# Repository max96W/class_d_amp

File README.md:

# Class D amplifier
A discrete class D amplifier able to deliver 300 W into 4 Ohms

For further information please read docu.pdf/odt. Note that the design is not fully tested yet so do not expect it to work out of the box if you like to build it.

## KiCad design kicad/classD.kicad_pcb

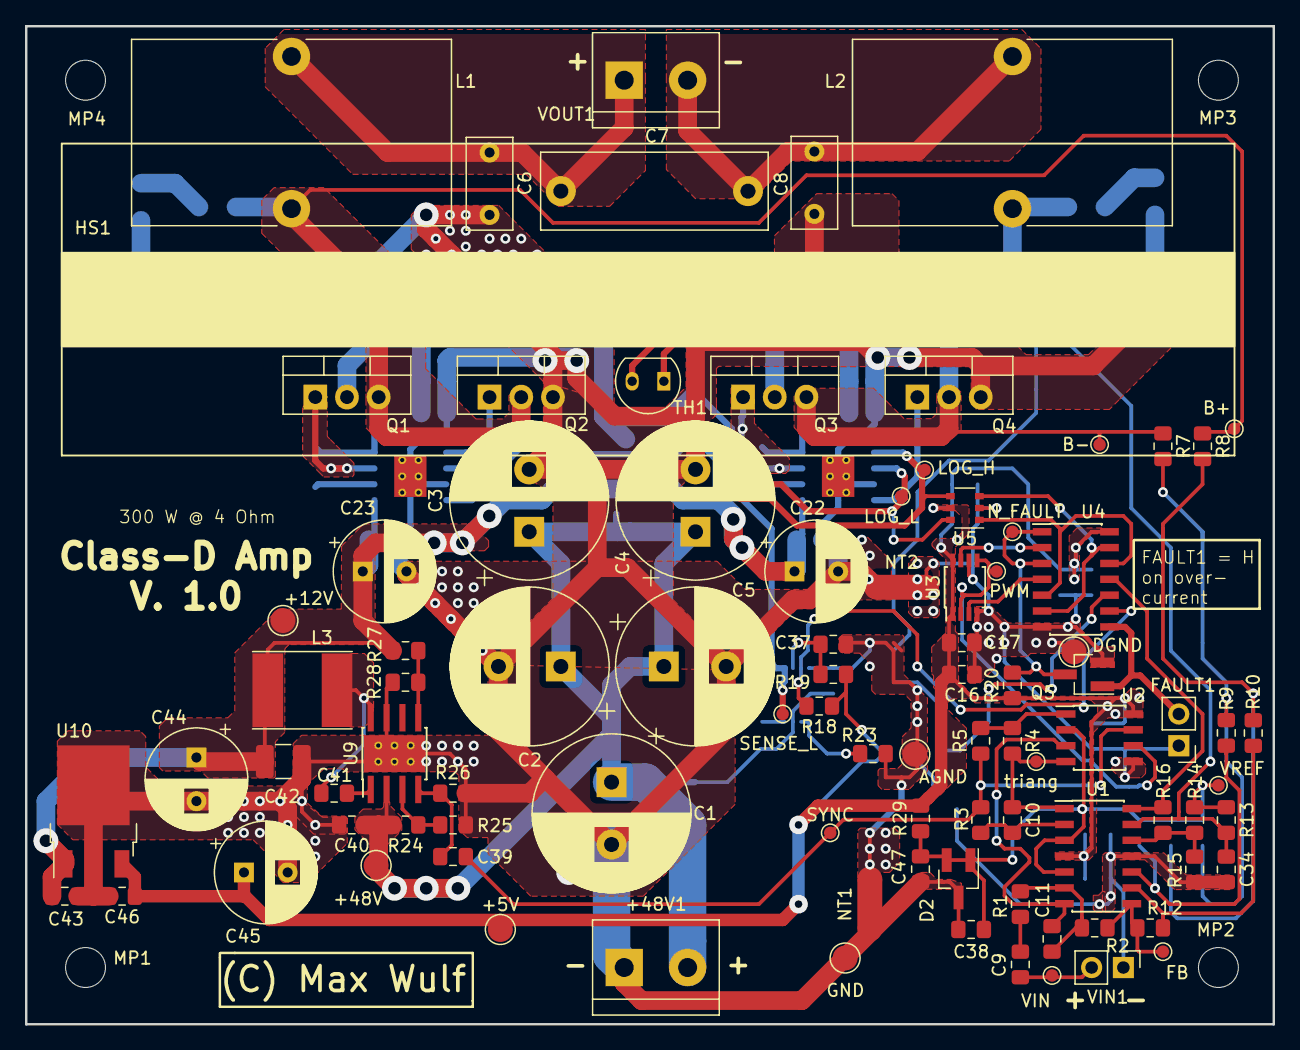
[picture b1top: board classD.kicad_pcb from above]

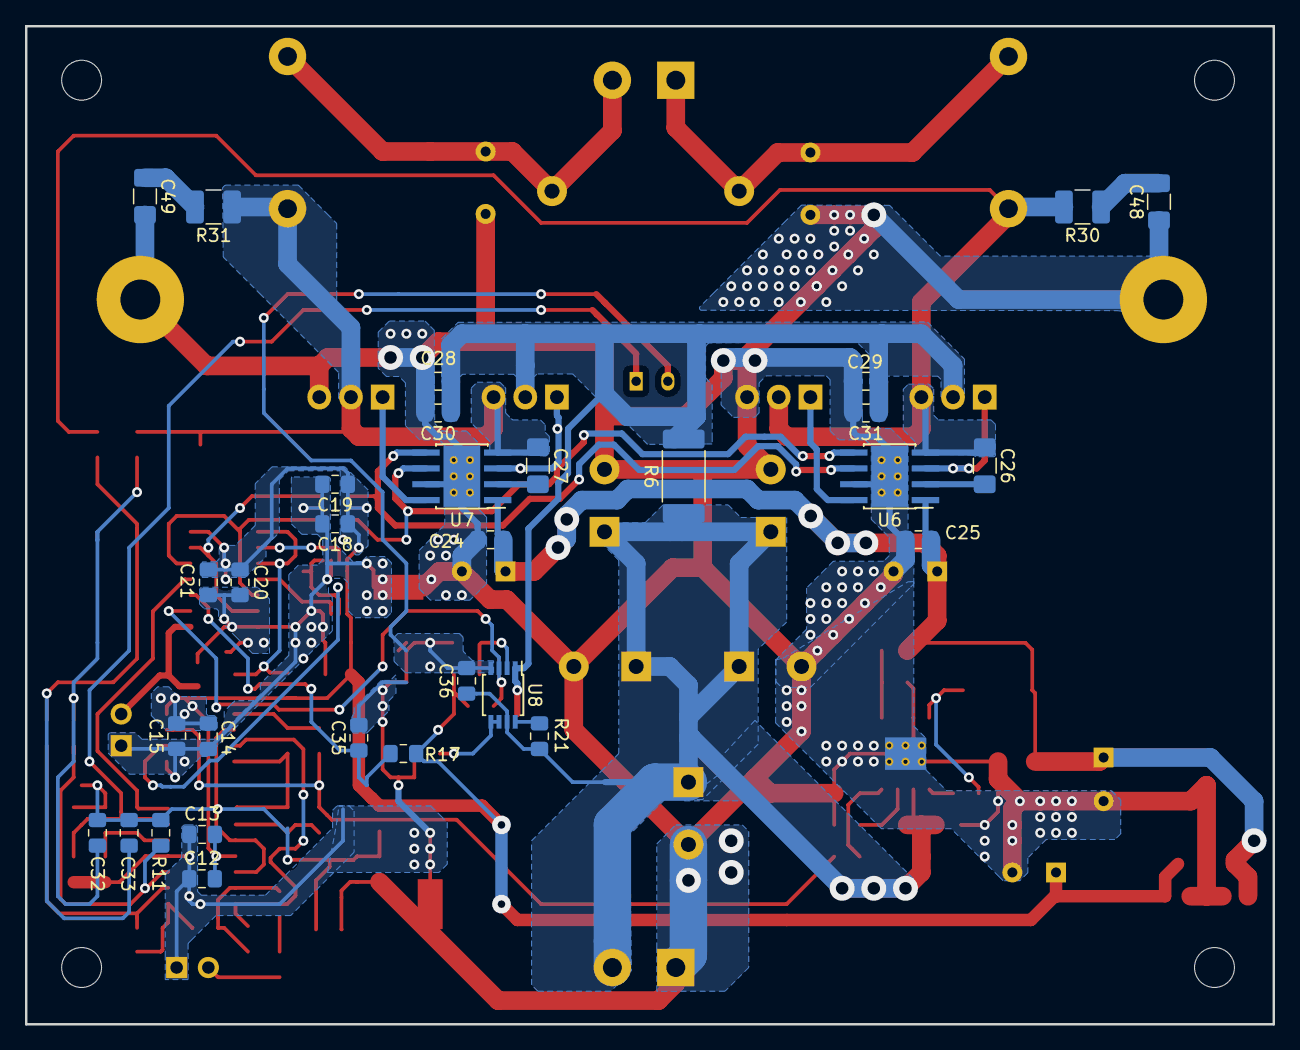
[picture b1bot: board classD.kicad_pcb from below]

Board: 2 copper layers, 100.0 x 80.0 mm, 128 parts (31 on the bottom side), 55 nets.

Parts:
+5V, +12V, +48V: TestPoint_Pad_D2.0mm
+48V1: 48V; TerminalBlock_bornier-2_P5.08mm
AGND: TestPoint_Pad_D2.0mm
B+: TestPoint_Pad_D1.0mm
B-: TestPoint_Pad_D1.0mm
C1, C2, C3, C4, C5: 470u/63V; CP_Radial_D12.5mm_P5.00mm
C6, C8: 270n/63 VDC; C_Rect_L7.2mm_W3.5mm_P5.00mm_FKS2_FKP2_MKS2_MKP2
C7: 1u/63 VAC; C_Rect_L18.0mm_W6.0mm_P15.00mm_FKS3_FKP3
C9: 2.2u; C_0805_2012Metric_Pad1.15x1.40mm_HandSolder
C10, C11: 33p; C_0805_2012Metric_Pad1.15x1.40mm_HandSolder
C12, C14, C16, C18, C20, C24, C25, C36, C37, C40, C41, C43, C46, C47: 100n; C_0805_2012Metric_Pad1.15x1.40mm_HandSolder
C13, C15, C17, C19, C21, C38: 10u; C_0805_2012Metric_Pad1.15x1.40mm_HandSolder
C22, C23, C44: 100u/25V; CP_Radial_D8.0mm_P3.50mm
C26, C27: 2.2u/63V; C_1206_3216Metric_Pad1.42x1.75mm_HandSolder
C28, C29: 100n/100V; C_0805_2012Metric_Pad1.15x1.40mm_HandSolder
C30, C31: 1u/100V; C_0805_2012Metric_Pad1.15x1.40mm_HandSolder
C32, C33: 6.8p; C_0805_2012Metric_Pad1.15x1.40mm_HandSolder
C34: 470n; C_0805_2012Metric_Pad1.15x1.40mm_HandSolder
C35: 4.7u; C_0805_2012Metric_Pad1.15x1.40mm_HandSolder
C39: 1n; C_0805_2012Metric_Pad1.15x1.40mm_HandSolder
C42: 22u; C_1210_3225Metric_Pad1.42x2.65mm_HandSolder
C45: 100u; CP_Radial_D8.0mm_P3.50mm
C48, C49: CZ; C_1206_3216Metric_Pad1.42x1.75mm_HandSolder
D2: TL431; SOT-23_Handsoldering
DGND: TestPoint_Pad_D2.0mm
FAULT1: Conn_01x02; PinHeader_1x02_P2.54mm_Vertical
FB: TestPoint_Pad_D1.0mm
GND: TestPoint_Pad_D2.0mm
HS1: ALUTRONIC_PR118-94-SE-M3
L1, L2: 15u; L_Toroid_Vertical_L25.4mm_W14.7mm_P12.20mm_Vishay_TJ5_BigPa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
L3: 220u; L_Taiyo-Yuden_NR-60xx_HandSoldering
LOG_H: TestPoint_Pad_D1.0mm
LOG_L: TestPoint_Pad_D1.0mm
MP1, MP2, MP3, MP4: MountingHole_3.2mm_M3
NT1, NT2: Net-Tie_2; NetTie-2_SMD_Pad2.0mm
N_FAULT: TestPoint_Pad_D1.0mm
PWM: TestPoint_Pad_D1.0mm
Q1, Q2, Q3, Q4: IRFB4020; TO-220-3_Vertical
Q5: BSS138; SOT-23_Handsoldering
R1: 43k; R_0805_2012Metric_Pad1.15x1.40mm_HandSolder
R2: 47k; R_0805_2012Metric_Pad1.15x1.40mm_HandSolder
R3, R5, R28: 22k; R_0805_2012Metric_Pad1.15x1.40mm_HandSolder
R4: 15k; R_0805_2012Metric_Pad1.15x1.40mm_HandSolder
R6: 20m/(1-2W); R_2512_6332Metric_Pad1.52x3.35mm_HandSolder
R7, R8: 2M; R_0805_2012Metric_Pad1.15x1.40mm_HandSolder
R9, R10, R11, R12: 56k; R_0805_2012Metric_Pad1.15x1.40mm_HandSolder
R13: 2.7k; R_0805_2012Metric_Pad1.15x1.40mm_HandSolder
R14, R15, R18, R20: 10k; R_0805_2012Metric_Pad1.15x1.40mm_HandSolder
R16, R17: 470k; R_0805_2012Metric_Pad1.15x1.40mm_HandSolder
R19: 100k; R_0805_2012Metric_Pad1.15x1.40mm_HandSolder
R21: 499; R_0805_2012Metric_Pad1.15x1.40mm_HandSolder
R23: 1k; R_0805_2012Metric_Pad1.15x1.40mm_HandSolder
R24, R25: 1M; R_0805_2012Metric_Pad1.15x1.40mm_HandSolder
R26: 49.9k; R_0805_2012Metric_Pad1.15x1.40mm_HandSolder
R27: 330k; R_0805_2012Metric_Pad1.15x1.40mm_HandSolder
R29: 120; R_0805_2012Metric_Pad1.15x1.40mm_HandSolder
R30, R31: RZ; R_1210_3225Metric_Pad1.42x2.65mm_HandSolder
SENSE_L: TestPoint_Pad_D1.0mm
SYNC: TestPoint_Pad_D1.0mm
TH1: KTY-210; TO-92-2
U1: OPA4350UA; SOIC-14_3.9x8.7mm_P1.27mm
U2: TLV3502; SOIC-8_3.9x4.9mm_P1.27mm
U3: SN74LVC2G86; TSSOP-8_3x3mm_P0.65mm
U4: 74HCT10; SOIC-14_3.9x8.7mm_P1.27mm
U5: SN74LVCG04; TSOP-6_1.65x3.05mm_P0.95mm
U6, U7: UCC27211; Texas_HTSOP-8-1EP_3.9x4.9mm_P1.27mm_EP2.95x4.9mm_Mask2.4x3.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
U8: LT6118; TSSOP-8_3x3mm_P0.65mm
U9: LMR16010; Texas_HTSOP-8-1EP_3.9x4.9mm_P1.27mm_EP2.95x4.9mm_Mask2.4x3.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
U10: MC78M05_TO252; TO-252-2
VIN: TestPoint_Pad_D1.0mm
VIN1: VIN; PinHeader_1x02_P2.54mm_Vertical
VOUT1: VOUT; TerminalBlock_bornier-2_P5.08mm
VREF: TestPoint_Pad_D1.0mm
triang: TestPoint_Pad_D1.0mm

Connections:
+5VD: +5V.1, C12.2, C13.2, C14.2, C15.2, C16.1, C17.1, C18.1, C19.1, C20.1, C21.1, C45.1, C46.1, R17.1, R18.1, R19.2, R20.1, R29.2, U1.4, U2.8, U3.1, U3.8, U4.14, U5.5, U10.3
+12V: +12V.1, C22.1, C23.1, C24.1, C25.1, C42.1, C43.1, C44.1, L3.2, R27.1, U6.1, U7.1, U10.1
+48V: +48V.1, +48V1.2, C1.1, C2.1, C3.1, C4.1, C5.1, C36.1, C40.1, R6.1, R21.1, R24.1, U8.7, U9.2
/bridge/LOG_H: LOG_H.1, U5.4, U6.6, U7.5
/bridge/LOG_L: LOG_L.1, U5.6, U6.5, U7.6
/bridge/SENSEL: C28.1, C29.1, C30.1, C31.1, Q1.2, Q3.2, R6.2, SENSE_L.1, U8.1
/dead_time/N_FAULT: N_FAULT.1, Q5.3, R20.2, U4.1, U4.3
/dead_time/PWM: PWM.1, U2.6, U3.2, U3.5
/feedback/B+: B+.1, C26.1, L1.2, Q1.3, Q2.2, R8.1, R30.2, U6.4
/feedback/B-: B-.1, C27.1, L2.2, Q3.3, Q4.2, R7.1, R31.1, U7.4
/feedback/FB: FB.1, R2.2, R12.2, U1.8
/feedback/VREF: C32.1, C33.2, C38.1, C47.1, D2.1, D2.2, R11.2, R13.1, R14.1, R29.1, U1.3, U1.5, U2.2, VREF.1
/modulator/SYNC: C39.2, R3.1, R5.1, SYNC.1, U2.7
/modulator/VIN: C9.2, VIN.1, VIN1.2
GND: +48V1.1, C1.2, C2.2, C3.2, C4.2, C5.2, C6.1, C8.2, C22.2, C23.2, C24.2, C25.2, C28.2, C29.2, C30.2, C31.2, C38.2, C40.2, C42.2, C43.2, C44.2, C45.2, C46.2, C47.2, C48.1, C49.2, D2.3, GND.1, HS1.1, NT1.1, NT2.1, Q2.3, Q4.3, R25.2, R26.2, R28.2, U6.7, U6.9, U7.7, U7.9, U9.7, U9.9, U10.2
GNDA: AGND.1, C12.1, C13.1, C34.2, C35.2, C36.2, C37.1, NT1.2, R15.2, R23.2, TH1.2, U1.11, U8.4, VIN1.1
GNDD: C14.1, C15.1, C16.2, C17.2, C18.2, C19.2, C20.2, C21.2, DGND.1, FAULT1.1, NT2.2, Q5.2, U2.5, U3.4, U3.6, U4.7, U5.2
unnamed: C6.2, C7.1, L1.1, VOUT1.1
unnamed: C7.2, C8.1, L2.1, VOUT1.2
unnamed: C9.1, R1.2
unnamed: C10.2, R3.2, U1.2
unnamed: C11.1, U1.7, U2.3
unnamed: C11.2, R1.1, R2.1, U1.6
unnamed: C26.2, U6.2
unnamed: C27.2, U7.2
unnamed: C32.2, R7.2, R9.1
unnamed: C33.1, R8.2, R10.1
unnamed: C34.1, R13.2, TH1.1, U1.13
unnamed: C35.1, R17.2, U4.10
unnamed: C37.2, R19.1, U8.2
unnamed: C39.1, R26.1, U9.4
unnamed: C41.1, U9.1
unnamed: C41.2, L3.1, U9.8
unnamed: C48.2, R30.1
unnamed: C49.1, R31.2
unnamed: FAULT1.2, Q5.1, U4.8
unnamed: Q1.1, U6.3
unnamed: Q2.1, U6.8
unnamed: Q3.1, U7.3
unnamed: Q4.1, U7.8
unnamed: R4.1, R5.2, U2.1
unnamed: R10.2, R12.1, U1.9
unnamed: R9.2, R11.1, U1.10
unnamed: R14.2, R15.1, R16.2, U1.12
unnamed: R16.1, U1.14, U4.11
unnamed: R18.2, U4.9, U8.3
unnamed: R21.2, U8.8
unnamed: R23.1, U8.5, U8.6
unnamed: R24.2, R25.1, U9.3
unnamed: R27.2, R28.1, U9.5
unnamed: U3.3, U4.4
unnamed: U3.7, U4.2
unnamed: U4.5, U4.12, U5.1
unnamed: U4.6, U4.13, U5.3
triang: C10.1, R4.2, U1.1, U2.4, triang.1

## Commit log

2019-07-14 Uploaded existing project
